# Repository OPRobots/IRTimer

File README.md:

# IRTimer: Maze & Line StopWatch

Cronómetro para MicroMouse y LineFollower con conectividad WiFi para visualización de interfaz gráfica web, permitiendo una simple integración con OBS y softwares similares. Además, tambien posee integración con nuestro sistema de inicio de robots [IRStart](https://github.com/OPRobots/IRStart), desde el cual se podrá detener y reiniciar el cronómetro a distancia.

## Módulo Principal y cronómetro de LineFollower

El módulo principal está pensado para situarse cerca de la línea del circuito para detectar el paso de los robots detectando su paso a través de un sensor infrarojo situado en la parte posterior del mismo.

Este módulo es el encargado de conectarse a la red WiFi local y montar un servidor web para la visualización de cronos en tiempo real. Este servidor web está pensado para poder integrarse de forma simple a modo de overlay en programas de streaming como OBS Studio para mostrar de forma más dinamica a la audiencia los tiempos de los robots. También será el encargado de recibir los comandos de inicio y parada desde los módulos de laberinto mediante ESP-NOW.

### Hardware
- **Microcontrolador**: ESP32-C3 supermini
- **Pantalla**: LCD de 135x240 RGB TFT (ST7789)
- **Sensor**: Sharp GP2Y0D815Z0F (15cm)
- **Receptor IR 38kHz**: TSSP77038TR
- **LEDs**: 2x LEDs RGB (WS2812B)
- **LiPo**: Batería 1S 1500mAh 523450

## Módulo MicroMouse

Estos módulos tienen un hardware muy similar al módulo principal, salvo porque no tienen botones ni pantalla. En este caso, el sensor está embebido dentro del propio poste para interferir lo mínimo posible con las lecturas del robot. Además, el diseño del poste permite multitud de colocaciones para facilitar el montaje en el laberinto.

Las paredes se comunican mediante ESP-NOW con el módulo principal enviando los comandos de START y STOP del cronómetro. Una vez la pared de inicio ha dado la señal, se queda inactiva hasta que se mantenga el sensor detectando por unos segundos para evitar que se inicie una nueva vuelta si el robot vuelve a la casilla inicial (sobre todo en reconocimiento).

### Hardware
- **Microcontrolador**: ESP32-C3 supermini
- **Sensor**: Sharp GP2Y0D815Z0F (15cm)
- **LEDs**: 2x LEDs RGB (WS2812B)
- **LiPo**: Batería 1S 1500mAh 523450

## PCB

Tiene un tamaño muy reducido, menos de 50x50mm, que permite encargarse en los principales fabricantes de PCB con acabado en Oro para más alucinancia. Además, también tiene un total de 6 capas, siendo la primera PCB de OPRobots en tener más de 2 capas.

Contiene los componentes necesarios para cargar la LiPo mediante el conector USB-C del propio ESP32, además de un lector de batería para avisar en caso de que la batería esté baja. Permite la conexión de los RGB tanto en vertical para el módulo principal como en horizontal para los módulos de laberinto.

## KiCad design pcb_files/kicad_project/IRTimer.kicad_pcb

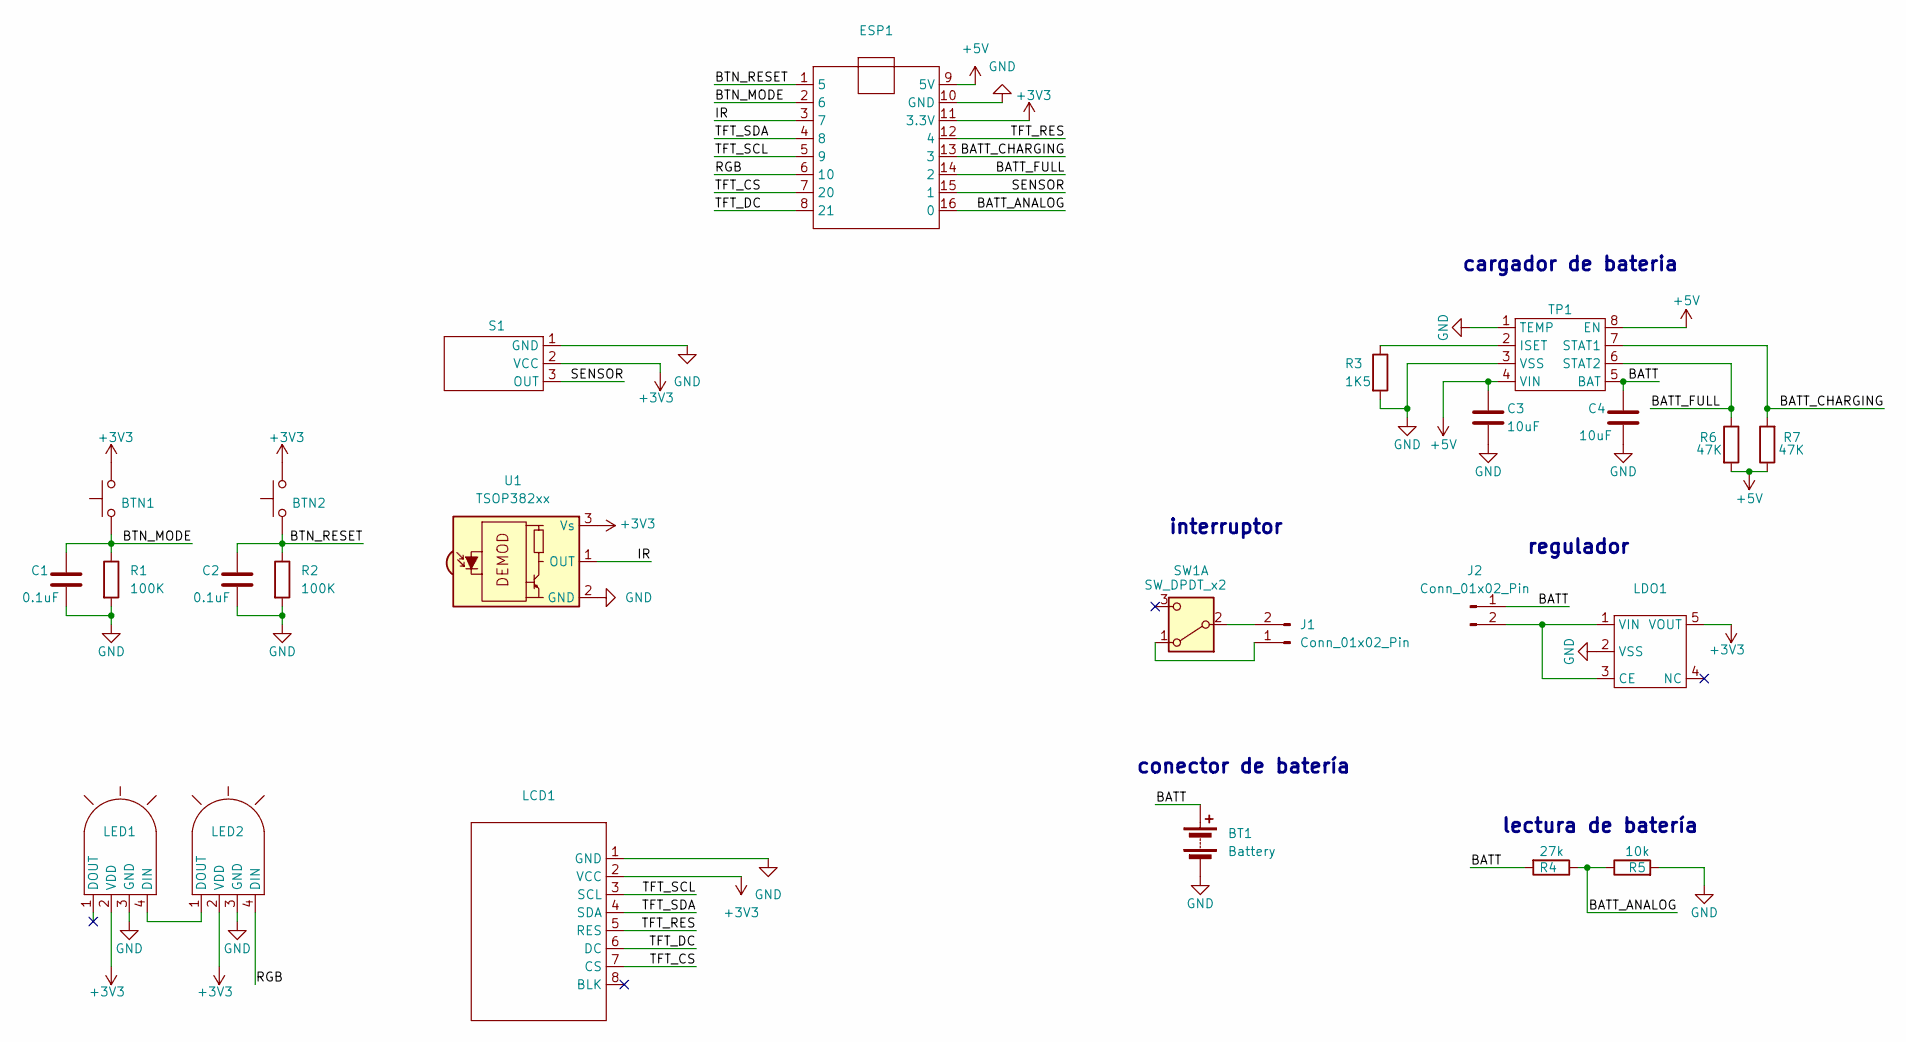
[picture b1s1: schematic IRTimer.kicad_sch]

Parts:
BT1: Battery; Leds_IR_Remote
BTN1, BTN2: SW_PUSH_6mm_H8mm
C1, C2: 0.1uF; C_0805_2012Metric_Pad1.18x1.45mm_HandSolder
C3, C4: 10uF; C_0805_2012Metric_Pad1.18x1.45mm_HandSolder
ESP1: ESP32_supermini
J1, J2: Conn_01x02_Pin; PinHeader_1x02_P2.54mm_Vertical
LCD1: ST7789V_LCD_RGB_135x240
LDO1: SOT-23-5_HandSoldering
LED1, LED2: LED_D5.0mm-4_RGB_Staggered_Pins
R1, R2: 100K; R_0805_2012Metric_Pad1.20x1.40mm_HandSolder
R3: 1K5; R_0805_2012Metric_Pad1.20x1.40mm_HandSolder
R4: 27k; R_0805_2012Metric_Pad1.20x1.40mm_HandSolder
R5: 10k; R_0805_2012Metric_Pad1.20x1.40mm_HandSolder
R6, R7: 47K; R_0805_2012Metric_Pad1.20x1.40mm_HandSolder
S1: PinHeader_1x03_P2.54mm_Vertical
SW1: SW_DPDT_x2; SW_SPDT_PCM12
TP1: SOP-8_3.9x4.9mm_P1.27mm
U1: TSOP382xx; IR TSOP38238 90º

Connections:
+3V3: BTN1.2, BTN2.2, ESP1.11 (3.3V), LCD1.2 (VCC), LDO1.5 (VOUT), LED1.2 (VDD), LED2.2 (VDD), S1.2 (VCC), U1.3 (Vs); also elsewhere on the board
+5V: C3.1, ESP1.9 (5V), R6.2, R7.1, TP1.4 (VIN), TP1.8 (EN)
/BATT: BT1.1 (+), C4.1, J2.1, R4.2, TP1.5 (BAT)
/BATT_ANALOG: ESP1.16 (0), R4.1, R5.1
/BATT_CHARGING: ESP1.13 (3), R7.2, TP1.7 (STAT1)
/BATT_FULL: ESP1.14 (2), R6.1, TP1.6 (STAT2)
/BTN_MODE: BTN1.1, C1.1, ESP1.2 (6), R1.1; also elsewhere on the board
/BTN_RESET: BTN2.1, C2.1, ESP1.1 (5), R2.1; also elsewhere on the board
/IR: ESP1.3 (7), U1.1 (OUT)
/RGB: ESP1.6 (10), LED2.4 (DIN)
/SENSOR: ESP1.15 (1), S1.3 (OUT)
/TFT_CS: ESP1.7 (20), LCD1.7 (CS)
/TFT_DC: ESP1.8 (21), LCD1.6 (DC)
/TFT_RES: ESP1.12 (4), LCD1.5 (RES)
/TFT_SCL: ESP1.5 (9), LCD1.3 (SCL)
/TFT_SDA: ESP1.4 (8), LCD1.4 (SDA)
GND: BT1.2 (-), C1.2, C2.2, C3.2, C4.2, ESP1.10 (GND), LCD1.1 (GND), LDO1.2 (VSS), LED1.3 (GND), LED2.3 (GND), R1.2, R2.2, R3.2, R5.2, S1.1 (GND), TP1.1 (TEMP), TP1.3 (VSS), U1.2 (GND)
unnamed: J1.1, SW1.1 (A)
unnamed: J1.2, SW1.2 (B)
unnamed: J2.2, LDO1.1 (VIN), LDO1.3 (CE)
unnamed: LED1.4 (DIN), LED2.1 (DOUT)
unnamed: R3.1, TP1.2 (ISET)

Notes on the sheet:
cargador de bateria
conector de batería
regulador
interruptor
lectura de batería

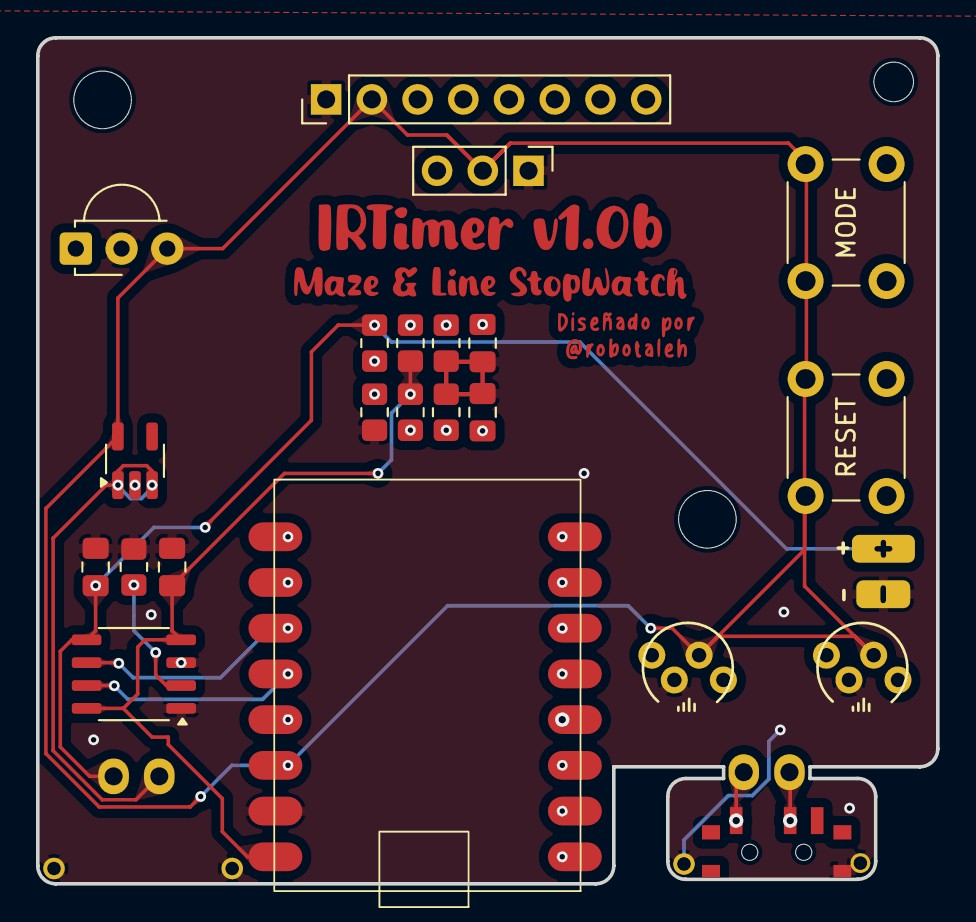
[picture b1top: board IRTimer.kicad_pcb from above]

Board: 6 copper layers, 50.0 x 47.0 mm, 25 parts (0 on the bottom side), 22 nets.

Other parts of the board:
MODE: SW_PUSH_6mm_H8mm
RESET: SW_PUSH_6mm_H8mm

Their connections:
+3V3: MODE.2, RESET.2; also elsewhere on the board
/BTN_MODE: MODE.1; also elsewhere on the board
/BTN_RESET: RESET.1; also elsewhere on the board

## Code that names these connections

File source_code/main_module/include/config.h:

#ifndef CONFIG_H
#define CONFIG_H

#include "rc5.h"
#include "screen.h"
#include "web.h"
#include <Arduino.h>

#define IR_PIN 7
#define SENSOR_PIN 1
#define NEOPIXEL_PIN 10

#define BTN_TOP_PIN 6
#define BTN_BOTTOM_PIN 5

#define BATT_CHARGING_PIN 3
#define BATT_FULL_PIN 2
#define BATT_VOLTAGE_PIN 0

#define TFT_MOSI 8 // SDA Pin on ESP32
#define TFT_SCLK 9 // SCL Pin on ESP32
#define TFT_CS 20  // Chip select control pin
#define TFT_DC 21  // Data Command control pin
#define TFT_RST 4  // Reset pin (could connect to RST pin)

void config_setup();

#endif

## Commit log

2024-12-25 Añade programas básicos del módulo principal y auxiliar
2024-12-26 Actualiza platformio.ini
2025-01-04 Añade v1.0 de la PCB
2025-01-04 Corrige gambada en el routeo de SCL y SDA de la TFT
2025-01-04 Añade template básica de cronómetro y splash screen
2025-01-05 Optimiza el mostrado del splash screen
2025-01-05 Añade visualización funcional de tiempos mediante TFT
2025-01-05 Añade lectura de botones
2025-01-06 Añade BOM de la PCB
2025-01-06 Inicia gestión de múltiple pantalla y modos
2025-01-15 Añade librarías y funciones básicas de Leds RGB
2025-01-15 Corrige velocidad de SPI de la TFT
2025-01-18 Actualiza NEOPIXEL_PIN en aux_module
2025-01-18 Añade lectura de batería y estado de la carga a main_module
2025-01-18 Corrige texto del botón de control_manage_screen
2025-01-19 Añade imagen de menú y cambio de pantallas
2025-01-19 Mejora el inicio y el menú de WiFi
2025-01-20 Muestra a toda pantalla el último tiempo de vuelta
2025-01-22 Añade gestiónde cronómetro mediante comandos RC5
2025-01-22 Actualiza MAC del módulo principal
2025-01-23 Añade gestión completa a los módulos auxiliares · Detección de pared mediante MAC · Envío de comandos de start y finish en función de la pared · Gestión de batería · Control de repetición de start
2025-01-23 Añade gestión de comandos de start y finish en el módulo principal
2025-01-23 Mejora la pantalla de tiempos y corrige bugs visuales
2025-02-27 Añade ajustes al main_module
2025-05-13 Añade redundancia de los envíos desde el client.cpp
2025-05-13 Deshabilita el sensor del módulo principal una vez se recibiese algún comando desde los auxiliares
2025-05-13 Actualiza README y añade imágenes
2025-05-20 Añade README de 3d_model
